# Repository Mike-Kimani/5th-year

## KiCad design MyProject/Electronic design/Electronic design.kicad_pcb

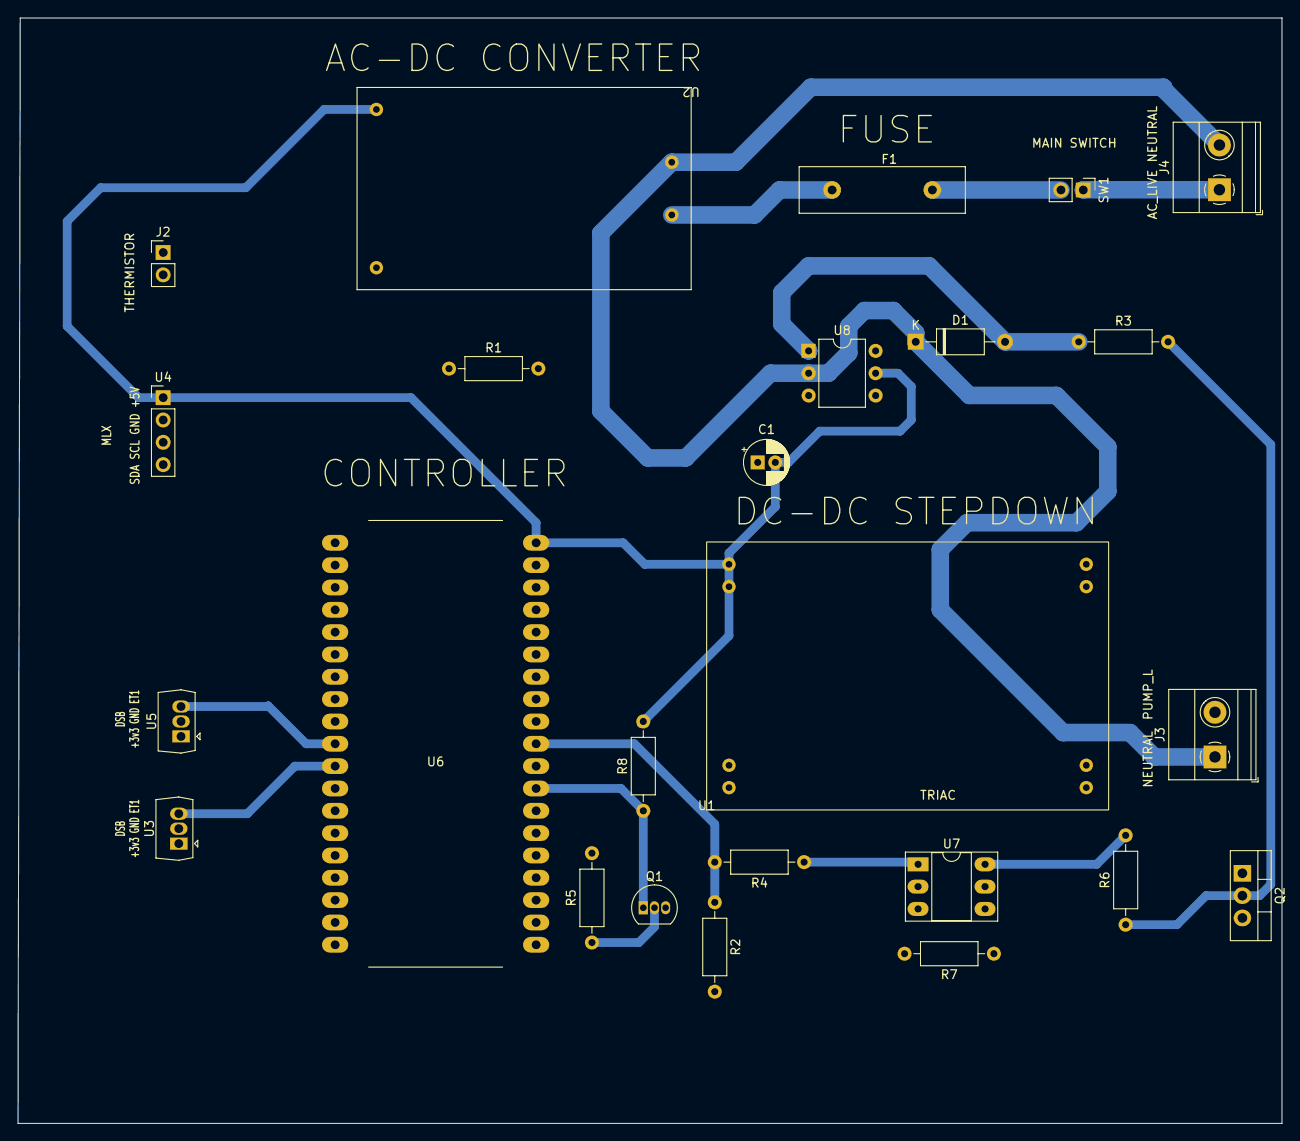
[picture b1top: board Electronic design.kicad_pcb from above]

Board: 2 copper layers, 143.8 x 125.7 mm, 25 parts (0 on the bottom side), 19 nets.

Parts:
C1: C_Small; CP_Radial_D5.0mm_P2.00mm
D1: 1N4007; D_A-405_P10.16mm_Horizontal
F1: 5A; Fuse_Littelfuse-LVR100
J2: Conn_01x02_Female; PinHeader_1x02_P2.54mm_Vertical
J3: Screw_Terminal_01x02; TerminalBlock_Phoenix_MKDS-1,5-2-5.08_1x02_P5.08mm_Horizont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
J4: TerminalBlock_Phoenix_MKDS-1,5-2-5.08_1x02_P5.08mm_Horizont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
Q1: BC547; TO-92_Inline
Q2: BT136-500; TO-220-3_Vertical
R1: 100K; R_Axial_DIN0207_L6.3mm_D2.5mm_P10.16mm_Horizontal
R2, R3, R4, R5, R7, R8: 330; R_Axial_DIN0207_L6.3mm_D2.5mm_P10.16mm_Horizontal
R6: 180; R_Axial_DIN0207_L6.3mm_D2.5mm_P10.16mm_Horizontal
SW1: SW_SPST; PinHeader_1x02_P2.54mm_Vertical
U1: MP1854
U2: AC-DC; AC_DC
U3: DSB1820; NEC_Molded_7x4x9mm
U4: MLX90614-ESF; PinHeader_1x04_P2.54mm_Vertical
U5: DSB18210; NEC_Molded_7x4x9mm
U6: ESP32-S
U7: MOC3021M; DIP-6_W7.62mm_Socket_LongPads
U8: 4N35; DIP-6_W7.62mm

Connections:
+3V3: R1.1, U1.7 (OUT+), U1.8 (OUT+), U3.1 (VCC), U5.1 (VCC)
+5V: C1.2, R8.2, U1.1 (IN+), U1.2 (IN+), U2.3 (VO+), U4.1 (VCC), U6.38 (+5V), U8.5
ACLIVE: J4.1, SW1.1 (A)
ET1: U3.3 (DAT), U6.11 (P18)
ET2: U5.3 (DAT), U6.10 (P5)
FUSEDACLIVE: F1.1, U2.1 (AC)
GND: C1.1, J2.2, Q1.3 (E), R2.2, R5.2, R7.2, U1.3 (IN-), U1.4 (IN-), U1.5 (OUT-), U1.6 (OUT-), U2.4 (VO-), U3.2 (GND), U4.2 (GND), U5.2 (GND), U6.19 (GND), U7.2
LIVE: Q2.2 (A2), R3.2, R6.1
NEUTRAL: D1.1 (A), J3.1, J4.2, U2.2 (AC), U8.2
unnamed: D1.2 (K), R3.1, U8.1
unnamed: F1.2, SW1.2 (B)
unnamed: J3.2, Q2.1 (A1)
unnamed: Q1.2 (B), R5.1, U8.4
unnamed: Q2.3 (G), R7.1, U7.4
unnamed: R4.1, U7.1
unnamed: R6.2, U7.6
PUMP: R2.1, R4.2, U6.29 (P26)
THERM: J2.1, R1.2, U6.34 (P13)
ZERO: Q1.1 (C), R8.1, U6.27 (P33)

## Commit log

2022-06-27 Units + Project files
2022-07-17 Electronic design + Reorganizing the repo
2022-07-21 Ignore mp4 files
2022-07-28 Shortening file names for Windows users
